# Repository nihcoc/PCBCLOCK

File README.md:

# PCBCLOCK by alfder

Schematics 

Front Layer 

Back Layer

3D Model

BOM

| Index | LCSC# | MPN | Manufacturer | Package | Customer # | Description | RoHS | Qty | MOQ | Multiple | Unit Price (USD) | Extended Price (USD) | Product Link |
|------:|:------|:----|:-------------|:--------|:-----------|:------------|:----:|----:|----:|---------:|-----------------:|---------------------:|:-------------|
| 1 | C1591 | CL10B104KB8NNNC | Samsung Electro-Mechanics | 0603 | | 100nF ±10% 50V Ceramic Capacitor X7R 0603 | Yes | 100 | 100 | 100 | 0.0242 | 2.42 | https://www.lcsc.com/product-detail/C1591.html |
| 2 | C5646000 | GJM1555C1H7R0WB01D | Murata | 0402 | | 7pF 50V Ceramic Capacitor | Yes | 10 | 10 | 10 | 0.0558 | 0.56 | https://www.lcsc.com/product-detail/C5646000.html |
| 3 | C41366936 | YLED0402P | YONGYUTAI | 0402 | | Purple LED, 2.6–3.0V | Yes | 50 | 50 | 50 | 0.0164 | 0.82 | https://www.lcsc.com/product-detail/C41366936.html |
| 4 | C19273152 | YLED0603Y | YONGYUTAI | 0603 | | Yellow LED, 1.8–2.4V | Yes | 100 | 100 | 100 | 0.0065 | 0.65 | https://www.lcsc.com/product-detail/C19273152.html |
| 5 | C475633 | BC849C | Shikues | SOT-23 | | NPN BJT Transistor, 45V, 100mA | Yes | 50 | 50 | 50 | 0.0177 | 0.89 | https://www.lcsc.com/product-detail/C475633.html |
| 6 | C95204 | RT0603BRD0710KL | YAGEO | 0603 | | 10kΩ ±0.1%, 100mW Thin Film Resistor | Yes | 20 | 20 | 20 | 0.0299 | 0.60 | https://www.lcsc.com/product-detail/C95204.html |
| 7 | C2689502 | PTS647SM38SMTR2LFS | C&K | SMD 4.5×4.5mm | | SPST-NO Tactile Switch, 180gf | Yes | 5 | 5 | 5 | 0.3402 | 1.70 | https://www.lcsc.com/product-detail/C2689502.html |
| 8 | C96514 | STM32L031G6U6 | STMicroelectronics | UFQFPN-28 (4×4mm) | | ARM Cortex-M0+, 32MHz MCU | Yes | 1 | 1 | 1 | 1.2214 | 1.22 | https://www.lcsc.com/product-detail/C96514.html |
| 9 | C5632699 | 7BG03276A1W | KDS | SMD1610-2P | | Crystal, 12.5pF, ±20ppm | Yes | 5 | 5 | 5 | 0.3400 | 1.70 | https://www.lcsc.com/product-detail/C5632699.html |

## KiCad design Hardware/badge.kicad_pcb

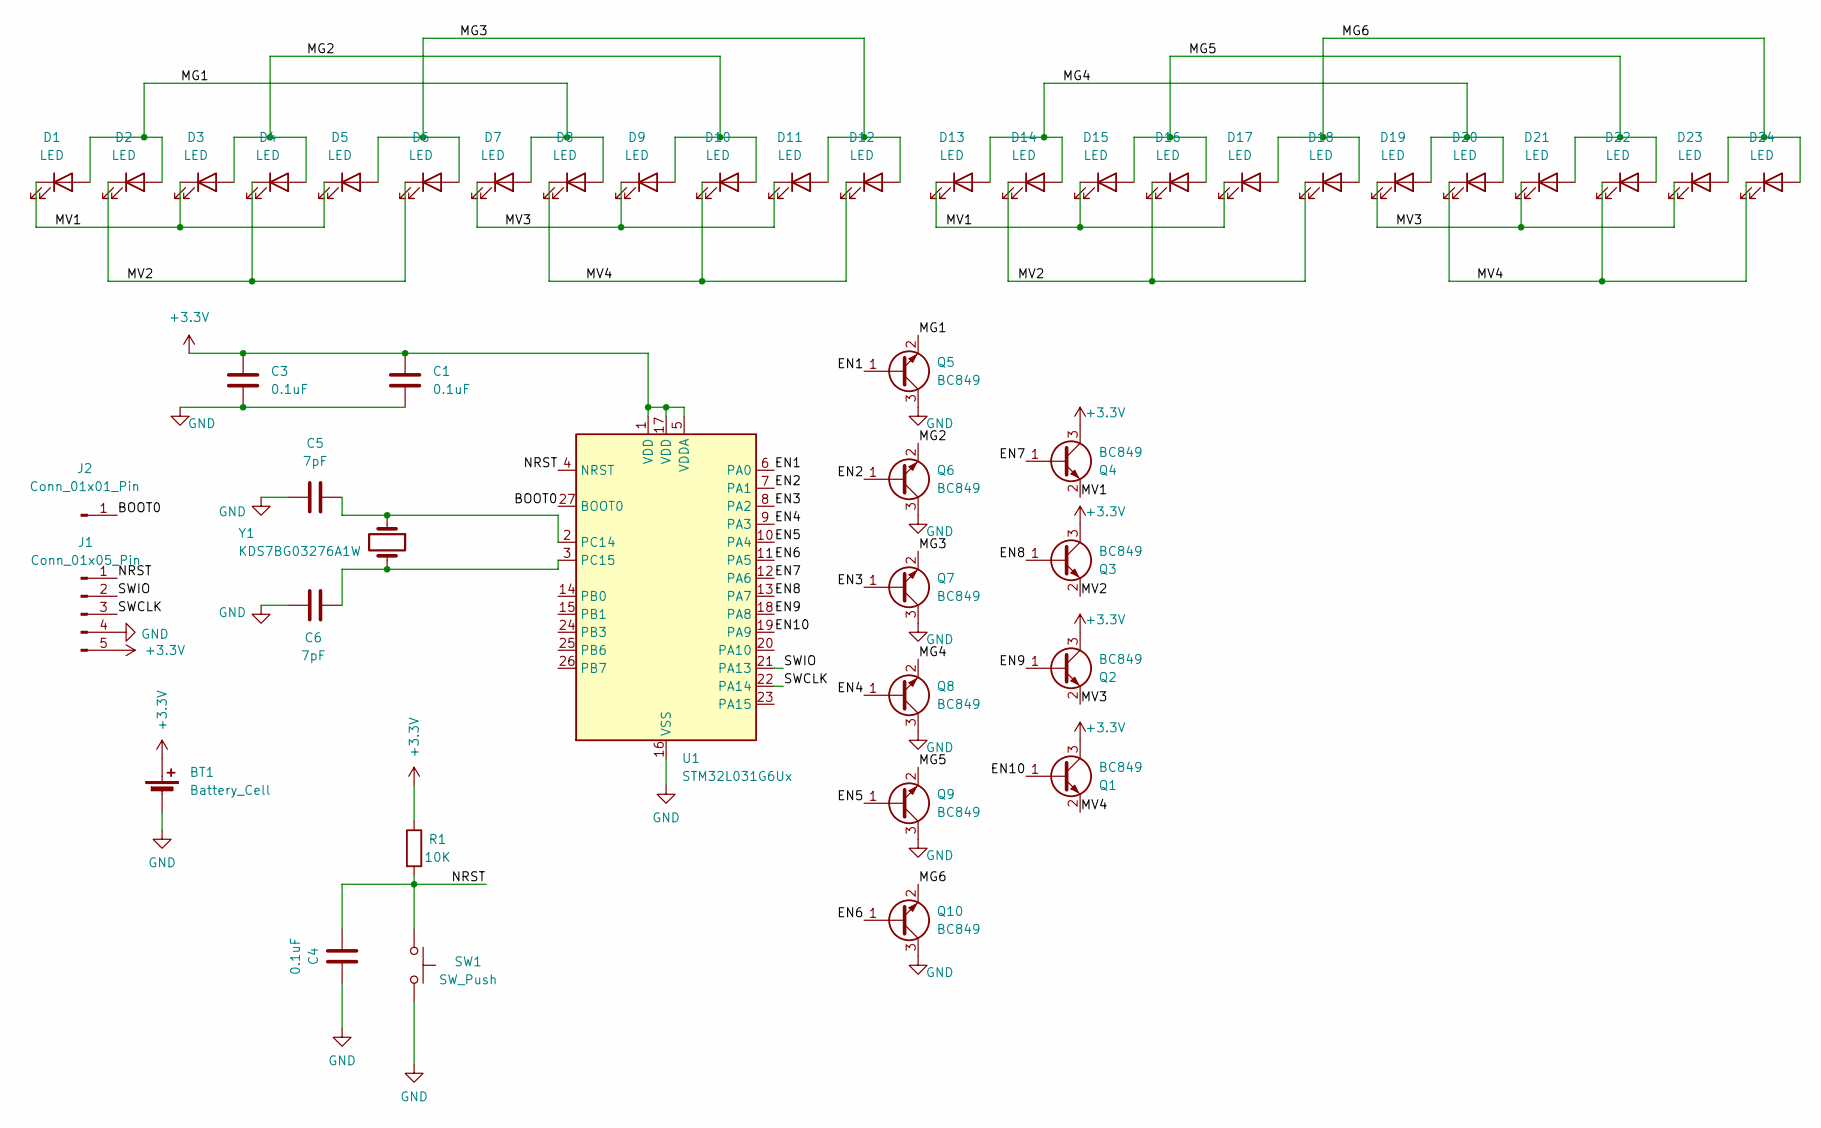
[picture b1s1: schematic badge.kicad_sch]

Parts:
BT1: Battery_Cell; BatteryHolder_MYOUNG_BS-07-A1BJ001_CR2032
C1, C3, C4: 0.1uF; C_0603_1608Metric
C5, C6: 7pF; C_0402_1005Metric
D1, D2, D3, D4, D5, D6, D7, D8, D9, D10, D11, D12, D13, D14, D15, D16, D17, D18, D19, D20, D21, D22, D23, D24: LED; LED_0402_1005Metric
J1: Conn_01x05_Pin; PinHeader_1x05_P2.54mm_Vertical
J2: Conn_01x01_Pin; PinHeader_1x01_P2.54mm_Vertical
Q1, Q2, Q3, Q4, Q5, Q6, Q7, Q8, Q9, Q10: BC849; SOT-23
R1: 10K; R_0603_1608Metric
SW1: SW_Push; SW_SPST_PTS647_Sx38
U1: STM32L031G6Ux; QFN-28_4x4mm_P0.5mm
Y1: KDS7BG03276A1W; XTAL_NX3215SA-32.768K-STD-MUA-14

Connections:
+3.3V: BT1.1 (+), C1.1, C3.1, J1.5, Q1.3 (C), Q2.3 (C), Q3.3 (C), Q4.3 (C), R1.1, U1.1 (VDD), U1.5 (VDDA), U1.17 (VDD)
/BOOT0: J2.1 (Pin_1_1), U1.27 (BOOT0)
/EN1: Q5.1 (B), U1.6 (PA0)
/EN2: Q6.1 (B), U1.7 (PA1)
/EN3: Q7.1 (B), U1.8 (PA2)
/EN4: Q8.1 (B), U1.9 (PA3)
/EN5: Q9.1 (B), U1.10 (PA4)
/EN6: Q10.1 (B), U1.11 (PA5)
/EN7: Q4.1 (B), U1.12 (PA6)
/EN8: Q3.1 (B), U1.13 (PA7)
/EN9: Q2.1 (B), U1.18 (PA8)
/EN10: Q1.1 (B), U1.19 (PA9)
/MG1: D1.2 (A), D2.2 (A), D7.2 (A), D8.2 (A), Q5.2 (E)
/MG2: D3.2 (A), D4.2 (A), D9.2 (A), D10.2 (A), Q6.2 (E)
/MG3: D5.2 (A), D6.2 (A), D11.2 (A), D12.2 (A), Q7.2 (E)
/MG4: D13.2 (A), D14.2 (A), D19.2 (A), D20.2 (A), Q8.2 (E)
/MG5: D15.2 (A), D16.2 (A), D21.2 (A), D22.2 (A), Q9.2 (E)
/MG6: D17.2 (A), D18.2 (A), D23.2 (A), D24.2 (A), Q10.2 (E)
/MV1: D1.1 (K), D3.1 (K), D5.1 (K), D13.1 (K), D15.1 (K), D17.1 (K), Q4.2 (E)
/MV2: D2.1 (K), D4.1 (K), D6.1 (K), D14.1 (K), D16.1 (K), D18.1 (K), Q3.2 (E)
/MV3: D7.1 (K), D9.1 (K), D11.1 (K), D19.1 (K), D21.1 (K), D23.1 (K), Q2.2 (E)
/MV4: D8.1 (K), D10.1 (K), D12.1 (K), D20.1 (K), D22.1 (K), D24.1 (K), Q1.2 (E)
/NRST: C4.1, J1.1, R1.2, SW1.1, U1.4 (NRST)
/SWCLK: J1.3, U1.22 (PA14)
/SWIO: J1.2, U1.21 (PA13)
GND: BT1.2 (-), C1.2, C3.2, C4.2, C5.1, C6.2, J1.4, Q5.3 (C), Q6.3 (C), Q7.3 (C), Q8.3 (C), Q9.3 (C), Q10.3 (C), SW1.2, U1.16 (VSS), U1.28 (VSS)
unnamed: C5.2, U1.2 (PC14), Y1.1
unnamed: C6.1, U1.3 (PC15), Y1.2

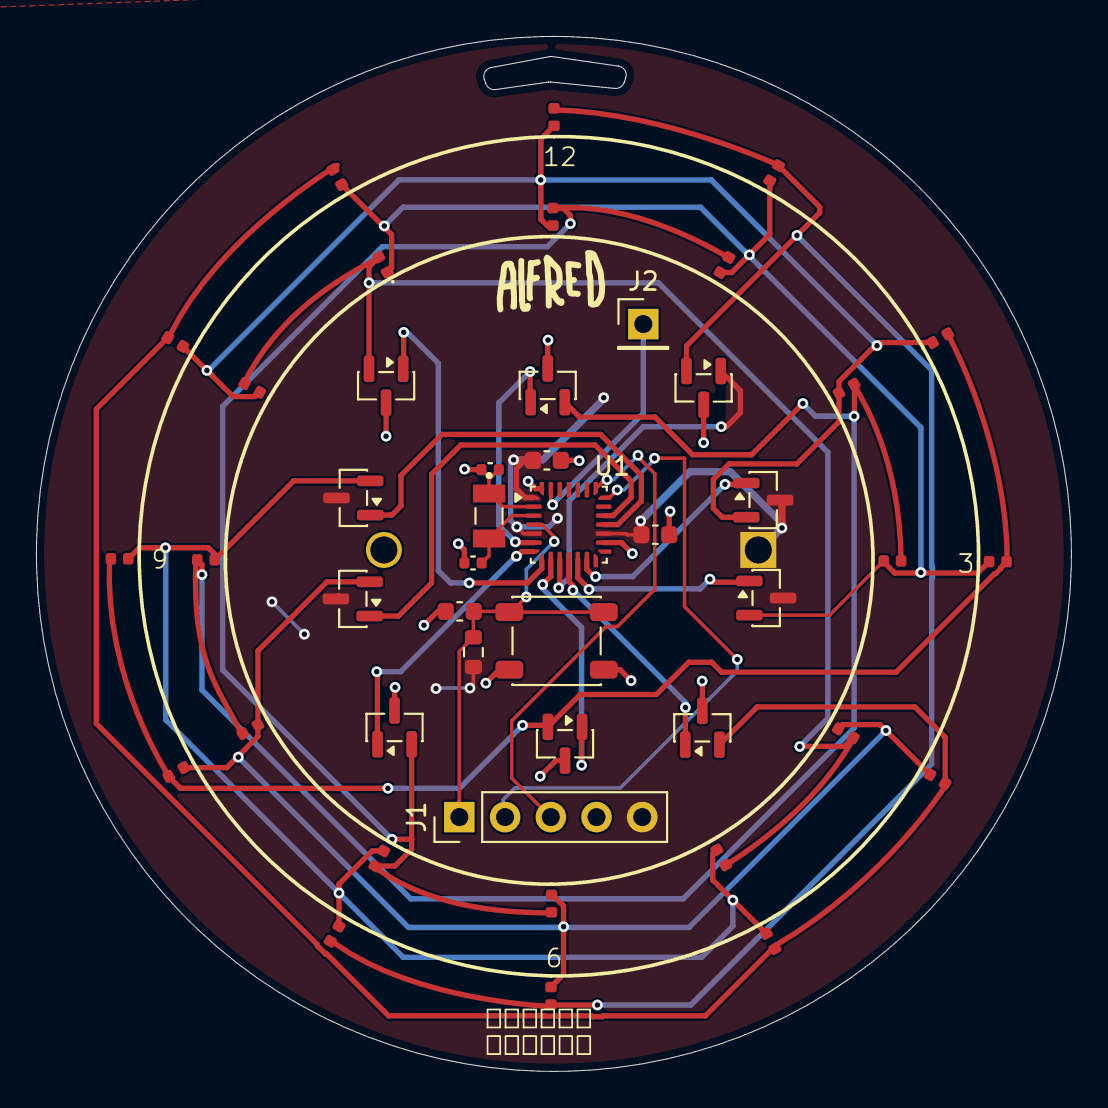
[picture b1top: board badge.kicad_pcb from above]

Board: 2 copper layers, 57.5 x 57.5 mm, 46 parts (1 on the bottom side), 28 nets.
